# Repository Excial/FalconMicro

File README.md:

# Falcon Micro Iterations

A robot design to navigate and inspect false ceilings

Security key: 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

==============================================================================

Completed: Falcon Lab V1

Issues: 

1. V reader sensor is not on the ADC pin, cannot get output
2. Accelerometer, gyroscope needs to be changed, from Serial to I2C
3. IMU I2C output needs to be transmitted to another MQTT directory
4. Motor encoders needed to adjust speed PWM, balance both motors
5. Rotational Motors need more torque, and encoders for balance
6. 8 more ADC channels required to communicate with Encoders 
7. Right Leg gets caught under track

==============================================================================

Completed: Falcon Micro Remote V1

1. Updates to arrive soon after assembly

==============================================================================

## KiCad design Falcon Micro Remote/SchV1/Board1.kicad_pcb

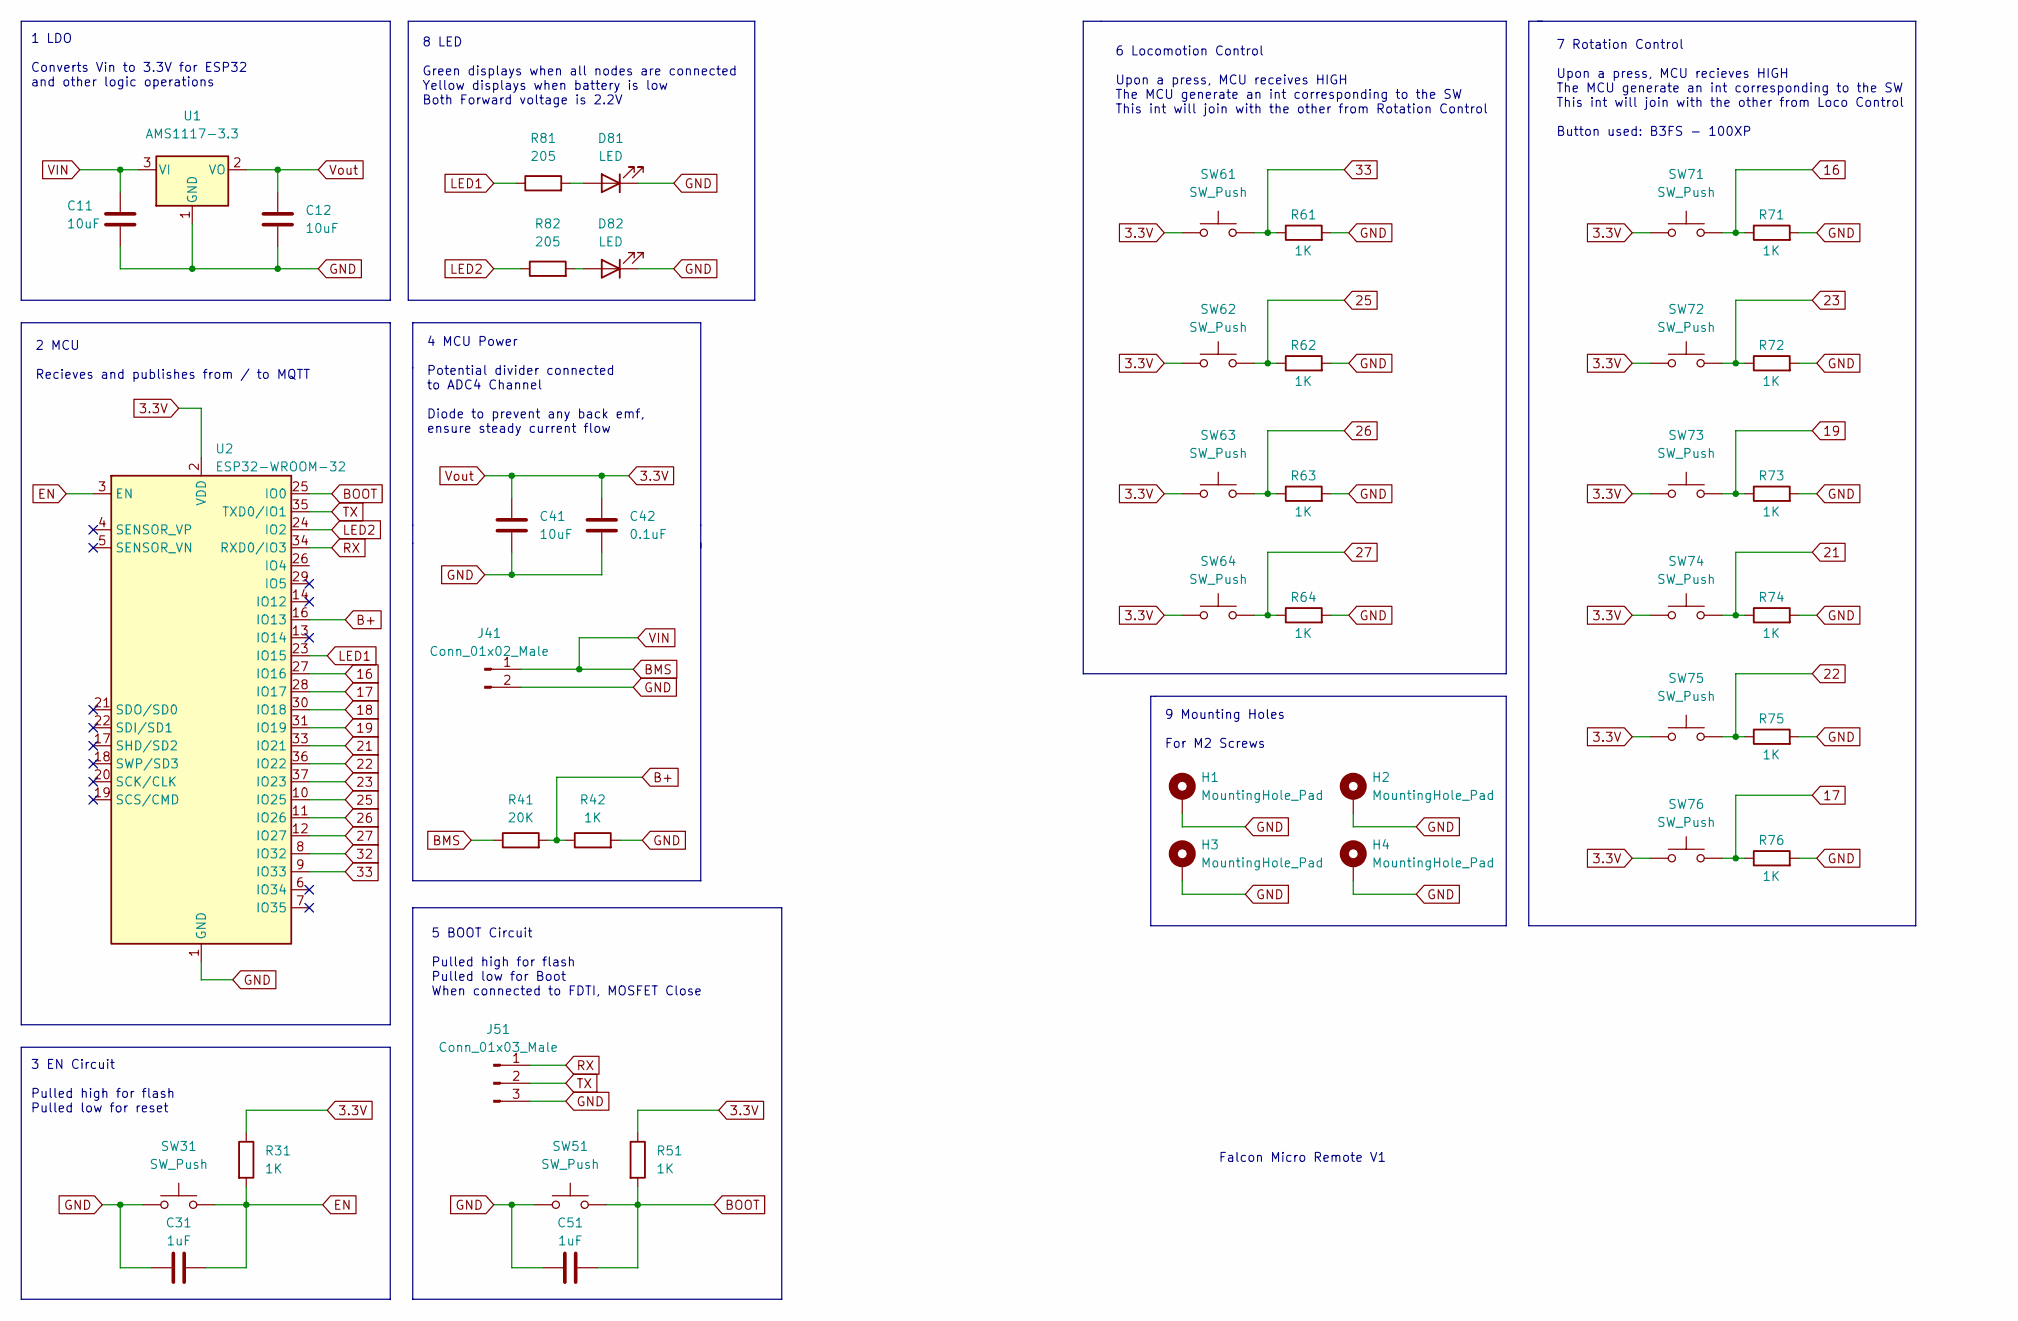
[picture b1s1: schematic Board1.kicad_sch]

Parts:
C11, C12, C41: 10uF; C_0201_0603Metric
C31, C51: 1uF; C_0201_0603Metric
C42: 0.1uF; C_0201_0603Metric
D81, D82: LED; LED_0201_0603Metric
H1, H2, H3, H4: MountingHole_Pad; MountingHole_2.2mm_M2_DIN965_Pad
J41: Conn_01x02_Male; PinSocket_1x02_P2.54mm_Vertical
J51: Conn_01x03_Male; PinSocket_1x03_P2.54mm_Vertical
R31, R42, R51, R61, R62, R63, R64, R71, R72, R73, R74, R75, R76: 1K; R_0402_1005Metric
R41: 20K; R_0402_1005Metric
R81, R82: 205; R_0402_1005Metric
SW31, SW51, SW61, SW62, SW63, SW64, SW71, SW72, SW73, SW74, SW75, SW76: SW_Push; SW_SPST_PTS645
U1: AMS1117-3.3; SOT-223-3_TabPin2
U2: ESP32-WROOM-32

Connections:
3.3V: C12.1, C41.1, C42.1, R31.1, R51.1, SW61.1, SW62.1, SW63.1, SW64.1, SW71.1, SW72.1, SW73.1, SW74.1, SW75.1, SW76.1, U1.2 (VO), U2.2 (VDD)
16: R71.1, SW71.2, U2.27 (IO16)
17: R76.1, SW76.2, U2.28 (IO17)
18: U2.30 (IO18)
19: R73.1, SW73.2, U2.31 (IO19)
21: R74.1, SW74.2, U2.33 (IO21)
22: R75.1, SW75.2, U2.36 (IO22)
23: R72.1, SW72.2, U2.37 (IO23)
25: R62.1, SW62.2, U2.10 (IO25)
26: R63.1, SW63.2, U2.11 (IO26)
27: R64.1, SW64.2, U2.12 (IO27)
32: U2.8 (IO32)
33: R61.1, SW61.2, U2.9 (IO33)
B+: R41.2, R42.1, U2.16 (IO13)
BOOT: C51.2, R51.2, SW51.2, U2.25 (IO0)
EN: C31.2, R31.2, SW31.2, U2.3 (EN)
GND: C11.2, C12.2, C31.1, C41.2, C42.2, C51.1, D81.1 (K), D82.1 (K), H1.1, H2.1, H3.1, H4.1, J41.2, J51.3, R42.2, R61.2, R62.2, R63.2, R64.2, R71.2, R72.2, R73.2, R74.2, R75.2, R76.2, SW31.1, SW51.1, U1.1 (GND), U2.1 (GND), U2.15 (GND), U2.38 (GND), U2.39 (GND)
LED1: R81.1, U2.23 (IO15)
LED2: R82.1, U2.24 (IO2)
unnamed: D81.2 (A), R81.2
unnamed: D82.2 (A), R82.2
RX: J51.1, U2.34 (RXD0/IO3)
TX: J51.2, U2.35 (TXD0/IO1)
VIN: C11.1, J41.1, R41.1, U1.3 (VI)

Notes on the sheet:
2 MCU Recieves and publishes from / to MQTT
8 LED Green displays when all nodes are connected Yellow displays when battery is low Both Forward voltage is 2.2V
5 BOOT Circuit Pulled high for flash Pulled low for Boot When connected to FDTI, MOSFET Close
Falcon Micro Remote V1
4 MCU Power Potential divider connected to ADC4 Channel Diode to prevent any back emf, ensure steady current flow
1 LDO Converts Vin to 3.3V for ESP32 and other logic operations
6 Locomotion Control Upon a press, MCU receives HIGH The MCU generate an int corresponding to the SW This int will join with the other from Rotation Control
9 Mounting Holes For M2 Screws
3 EN Circuit Pulled high for flash Pulled low for reset
7 Rotation Control Upon a press, MCU recieves HIGH The MCU generate an int corresponding to the SW This int will join with the other from Loco Control Button used: B3FS - 100XP

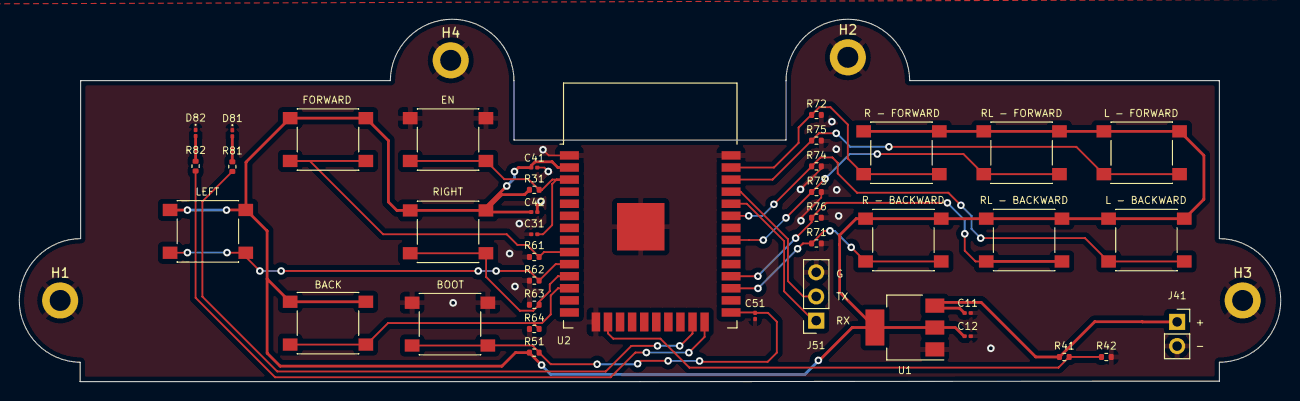
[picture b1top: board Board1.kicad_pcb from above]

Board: 2 copper layers, 132.6 x 38.1 mm, 44 parts (0 on the bottom side), 22 nets.

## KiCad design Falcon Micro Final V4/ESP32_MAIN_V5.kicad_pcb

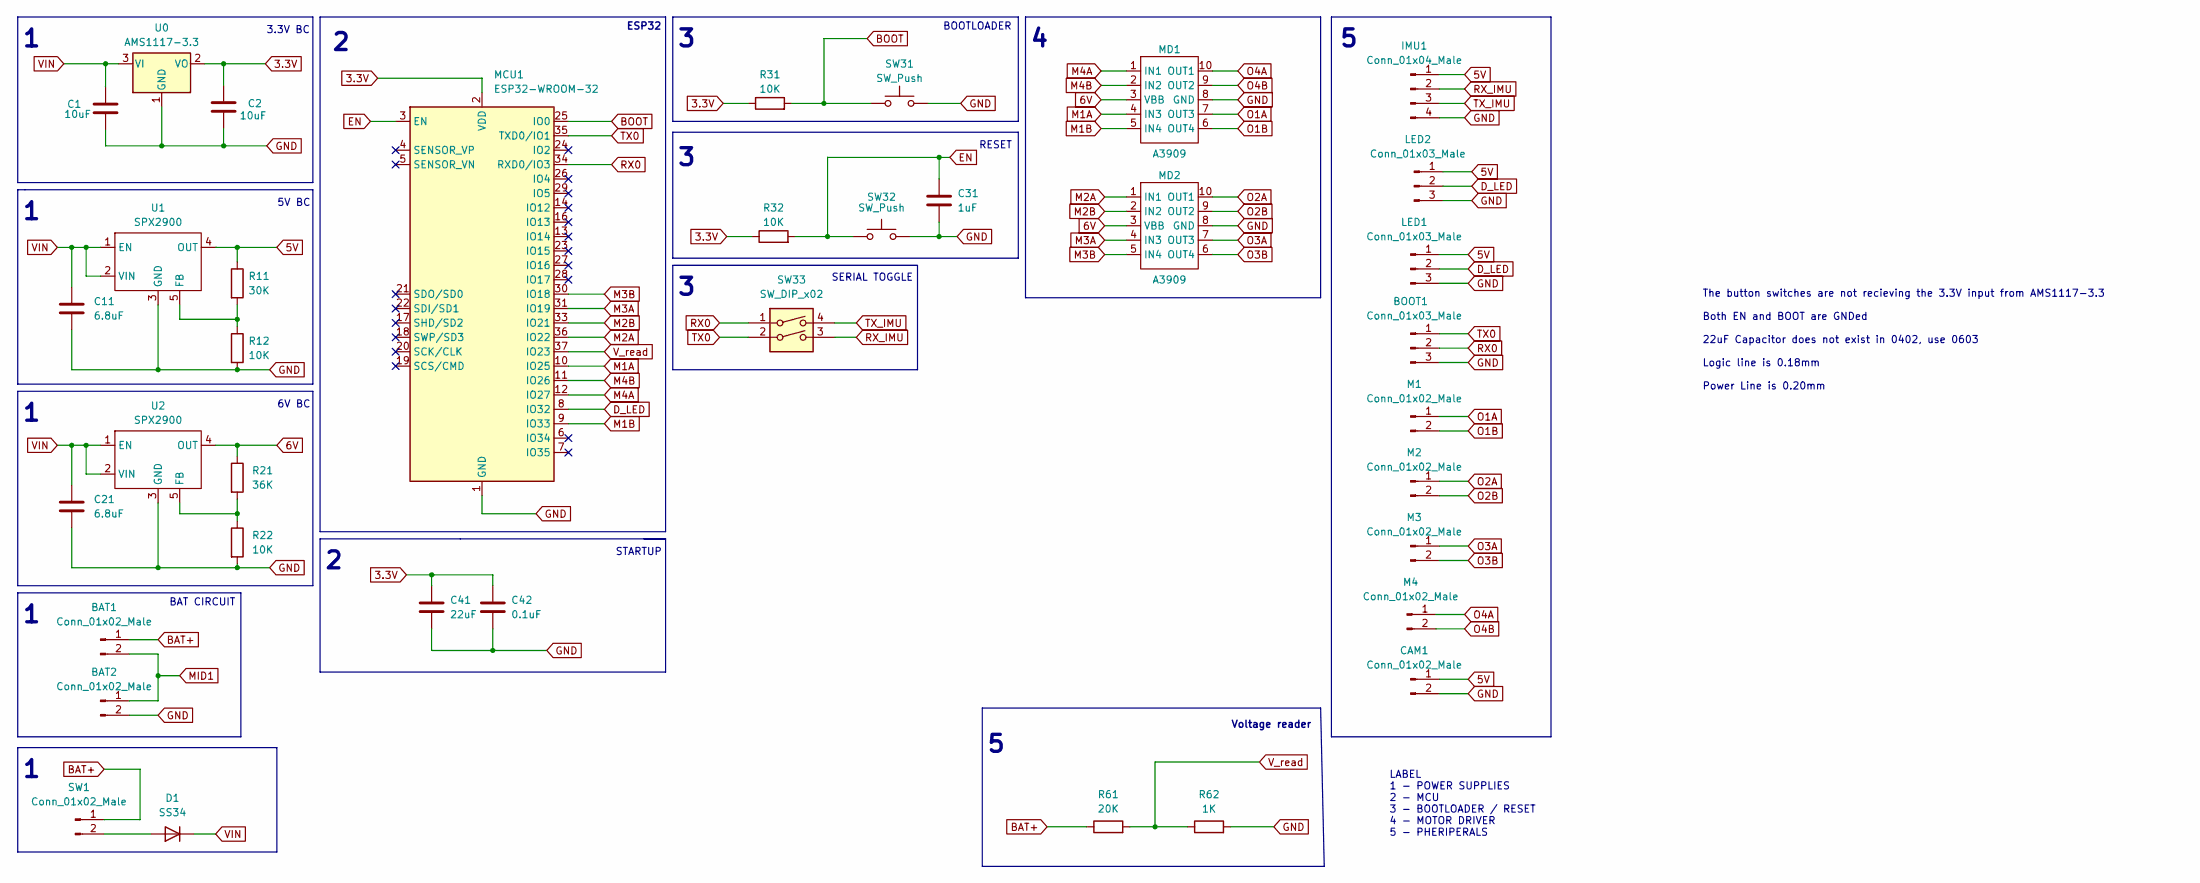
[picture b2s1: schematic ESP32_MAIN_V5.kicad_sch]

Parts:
BAT1, BAT2: Conn_01x02_Male; PinHeader_1x02_P2.54mm_Vertical
BOOT1: Conn_01x03_Male; PinHeader_1x03_P2.54mm_Vertical
C1, C2: 10uF; C_0402_1005Metric_Pad0.74x0.62mm_HandSolder
C11, C21: 6.8uF; CP_Elec_4x5.8
C31: 1uF; C_0402_1005Metric_Pad0.74x0.62mm_HandSolder
C41: 22uF; C_0603_1608Metric_Pad1.08x0.95mm_HandSolder
C42: 0.1uF; C_0402_1005Metric_Pad0.74x0.62mm_HandSolder
CAM1: Conn_01x02_Male; PinHeader_1x02_P2.54mm_Vertical
D1: SS34; D_SMA
IMU1: Conn_01x04_Male; PinHeader_1x04_P2.54mm_Vertical
LED1, LED2: Conn_01x03_Male; PinHeader_1x03_P2.54mm_Vertical
M1, M2, M3, M4: Conn_01x02_Male; PinHeader_1x02_P2.54mm_Vertical
MCU1: ESP32-WROOM-32
MD1, MD2: A3909; SSOP-10_3.9x4.9mm_P1.00mm
R11: 30K; R_0402_1005Metric
R12, R22, R31, R32: 10K; R_0402_1005Metric
R21: 36K; R_0402_1005Metric
R61: 20K; R_0402_1005Metric
R62: 1K; R_0402_1005Metric
SW1: Conn_01x02_Male; PinHeader_1x02_P2.54mm_Vertical
SW31, SW32: SW_Push; SW_SPST_Omron_B3FS-100xP
SW33: SW_DIP_x02; SW_DIP_SPSTx02_Slide_Omron_A6H-2101_W6.15mm_P1.27mm
U0: AMS1117-3.3; SOT-223-3_TabPin2
U1, U2: SPX2900; TO-263-5_TabPin3

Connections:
3.3V: C2.2, C41.1, C42.1, MCU1.2 (VDD), R31.1, R32.1, U0.2 (VO)
5V: CAM1.1, IMU1.1, LED1.1, LED2.1, R11.1, U1.4 (OUT)
6V: MD1.3 (VBB), MD2.3 (VBB), R21.1, U2.4 (OUT)
BAT+: BAT1.1, R61.1, SW1.1
BOOT: MCU1.25 (IO0), R31.2, SW31.1
D_LED: LED1.2, LED2.2, MCU1.8 (IO32)
EN: C31.1, MCU1.3 (EN), R32.2, SW32.1
GND: BAT2.2, BOOT1.3, C1.1, C2.1, C11.2, C21.2, C31.2, C41.2, C42.2, CAM1.2, IMU1.4, LED1.3, LED2.3, MCU1.1 (GND), MCU1.15 (GND), MCU1.38 (GND), MCU1.39 (GND), MD1.8 (GND), MD2.8 (GND), R12.2, R22.2, R62.2, SW31.2, SW32.2, U0.1 (GND), U1.3 (GND), U2.3 (GND)
M1A: MCU1.10 (IO25), MD1.4 (IN3)
M1B: MCU1.9 (IO33), MD1.5 (IN4)
M2A: MCU1.36 (IO22), MD2.1 (IN1)
M2B: MCU1.33 (IO21), MD2.2 (IN2)
M3A: MCU1.31 (IO19), MD2.4 (IN3)
M3B: MCU1.30 (IO18), MD2.5 (IN4)
M4A: MCU1.12 (IO27), MD1.1 (IN1)
M4B: MCU1.11 (IO26), MD1.2 (IN2)
MID1: BAT1.2, BAT2.1
unnamed: D1.2 (A), SW1.2
unnamed: R11.2, R12.1, U1.5 (FB)
unnamed: R21.2, R22.1, U2.5 (FB)
O1A: M1.1, MD1.7 (OUT3)
O1B: M1.2, MD1.6 (OUT4)
O2A: M2.1, MD2.10 (OUT1)
O2B: M2.2, MD2.9 (OUT2)
O3A: M3.1, MD2.7 (OUT3)
O3B: M3.2, MD2.6 (OUT4)
O4A: M4.1, MD1.10 (OUT1)
O4B: M4.2, MD1.9 (OUT2)
RX0: BOOT1.2, MCU1.34 (RXD0/IO3), SW33.1
RX_IMU: IMU1.2, SW33.3
TX0: BOOT1.1, MCU1.35 (TXD0/IO1), SW33.2
TX_IMU: IMU1.3, SW33.4
VIN: C1.2, C11.1, C21.1, D1.1 (K), U0.3 (VI), U1.1 (EN), U1.2 (VIN), U2.1 (EN), U2.2 (VIN)
V_read: MCU1.37 (IO23), R61.2, R62.1

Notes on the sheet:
5V BC
STARTUP
Voltage reader
The button switches are not recieving the 3.3V input from AMS1117-3.3 Both EN and BOOT are GNDed 22uF Capacitor does not exist in 0402, use 0603 Logic line is 0.18mm Power Line is 0.20mm
RESET
SERIAL TOGGLE
6V BC
BOOTLOADER
BAT CIRCUIT
3.3V BC
LABEL 1 - POWER SUPPLIES 2 - MCU 3 - BOOTLOADER / RESET 4 - MOTOR DRIVER 5 - PHERIPERALS
ESP32

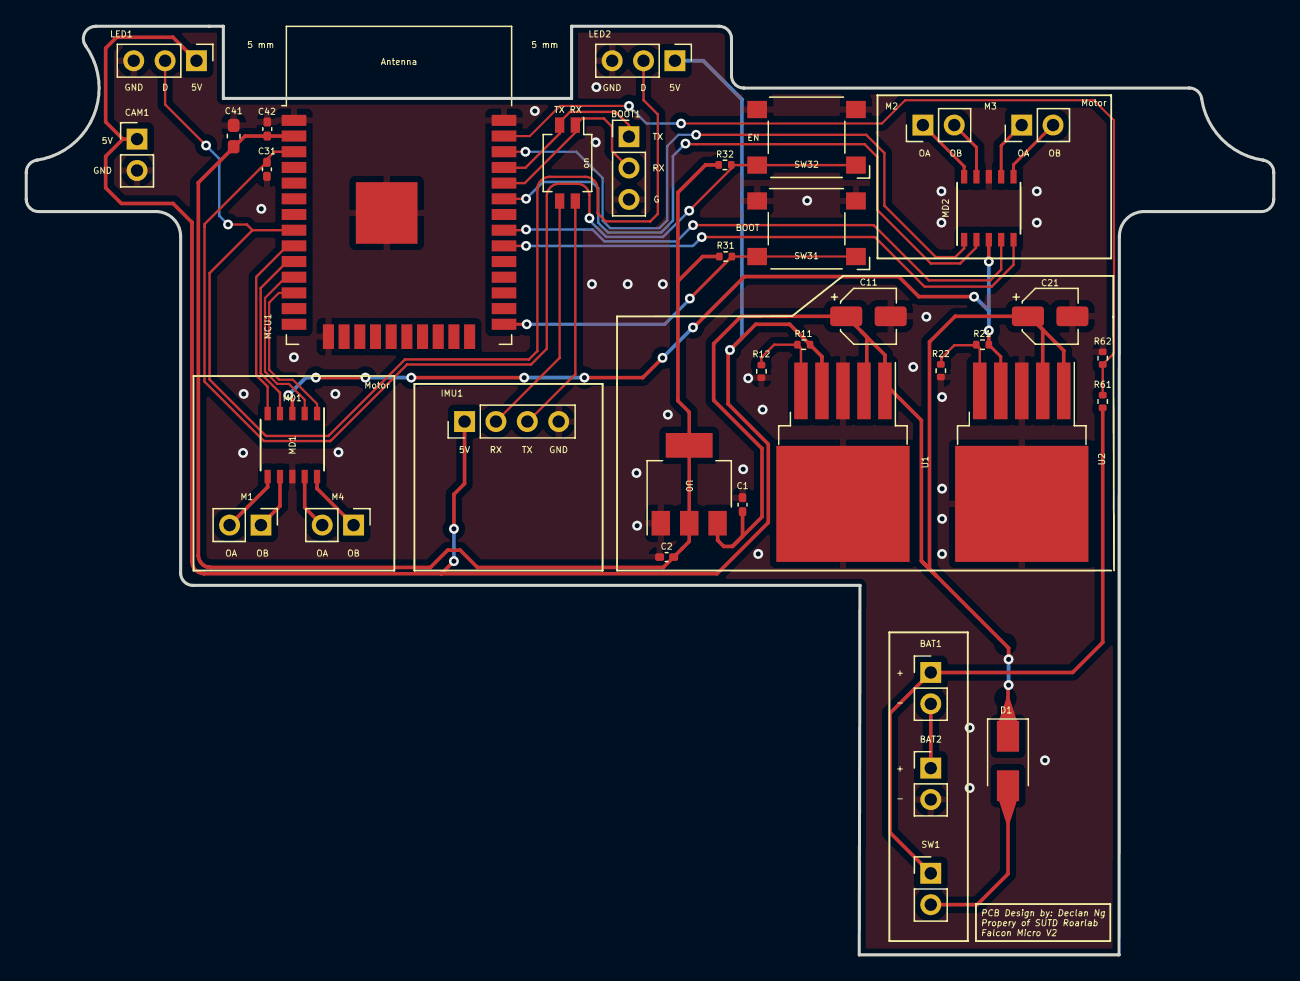
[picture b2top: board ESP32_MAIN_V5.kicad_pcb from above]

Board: 2 copper layers, 101.0 x 75.2 mm, 37 parts (0 on the bottom side), 34 nets.

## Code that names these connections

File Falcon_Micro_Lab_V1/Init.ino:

void init_ser() {

  Serial.begin(9600);
  Serial.println("SERIAL DONE");

}

void init_vbat()  {

  pinMode(23, INPUT);
  Serial.println("VBAT DONE");
}

void init_wifi()  {

  WiFi.begin(ssid);

  while (WiFi.status() != WL_CONNECTED) {
    delay(500);
    Serial.println("Connecting to WiFi..");
  }

  Serial.println("Connected to the WiFi network");

  client.setServer(mqttServer, mqttPort);
  client.setCallback(callback);

  while (!client.connected()) {

    Serial.println("Connecting to MQTT...");

    if (client.connect("ESP32Client", mqttUser, mqttPassword )) {

      client.subscribe("falcon/micro1");
      client.subscribe("falcon/imu1");

      Serial.println("connected");

    } else {

      Serial.print("failed with state ");
      Serial.print(client.state());
      delay(2000);

    }
  }
}

void init_led() {

  strip.begin();
  strip.setBrightness(BRIGHTNESS);

  strip.setPixelColor(0, 0, 0, 120);
  strip.setPixelColor(1, 0, 0, 120);
  strip.show();

}

void init_md()  {

  //Initialise all Motor drivers
  //In case the MDs cannot start

  ledcSetup(0, freq, resolution);
  ledcSetup(1, freq, resolution);
  ledcSetup(2, freq, resolution);
  ledcSetup(3, freq, resolution);
  ledcSetup(4, freq, resolution);
  ledcSetup(5, freq, resolution);
  ledcSetup(6, freq, resolution);
  ledcSetup(7, freq, resolution);

  ledcAttachPin(M1A, 0);
  ledcAttachPin(M1B, 1);
  ledcAttachPin(M2A, 2);
  ledcAttachPin(M2B, 3);
  ledcAttachPin(M3A, 4);
  ledcAttachPin(M3B, 5);
  ledcAttachPin(M4A, 6);
  ledcAttachPin(M4B, 7);

}

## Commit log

2022-07-25 New file updates for the latest versions of Falcon_Micro
2022-07-25 New files for the Falcon Micro Remote console, refer to internal notes on .sch to find updates
2022-07-25 None
2022-07-26 Updated with new Remote files
2022-07-26 Added Sch, Added Brd, added all footprint links. New items added to sch, need to link Board outline not decided
2022-07-26 Changed names
2022-07-27 Made modifications to sch and brd files
2022-07-27 Changed Key on Readme
2022-07-28 Remote V1 has been sent for fabrication, fab project completed Will start on falcon Mini Lab V3, and Remote V2 next iteration
2022-07-28 Some file edits, readme changes, not major
2022-07-29 Modified some of the sch files, preparing for V2
2022-07-29 Some file movements, so that everything is neater
2022-08-11 Modified some files, pushing to keep things up to date
